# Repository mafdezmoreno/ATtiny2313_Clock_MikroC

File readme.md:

# 7 Segments Display Clock

DIY clock using seven-segment display, ATtiny2313A and optionaly an DHT sensor.

# Structure of this repository

* CAD Files (STL).
* Code for Mikro C Proyect.
* KiCAD proyect with schematic and PCB Design.

## Prerequisites

To carry out this project, it is essential to have a PCB (the one attached in this project or a similar one) in which to solder all the components.

The circuit can also be mounted in an equivalent way on a breadboard following the connection diagram.

A series of electronic components are needed. Below are the recommended components for the realization of the project. Some of them can be replaced by equivalent ones, for example: the value of the resistors, capacitors, mcu (also fucniona with the ATtiny2313), etc.

Compilation and programming tools are also needed. Below are the recommended ones

### Components

List of electronics component nedded:

1. ATtiny2313 (or equivalent)
2. Crystal quartz oscilator 11.0Mhz
3. 4 Digit seven segment display
4. 22pF capacitors
5. Resistor (view schematic)
6. Button switches
7. Some pin 2.54mm connectors 

### Tools needed

1. Programmer. I've used a (Pololu USB AVR Programmer v2)[https://www.pololu.com/product/3170], but you can use another one compatible with the mcu (PICkit, AVRISP XPII... )
2. Compiler. Mikro C AVR Compiler. There are a free versión limited by de memory size of the program to burn into de mcu.
3. Software to load hex file into mcu, using a programmer. I've used (AVRDudess)[https://blog.zakkemble.net/avrdudess-a-gui-for-avrdude/]

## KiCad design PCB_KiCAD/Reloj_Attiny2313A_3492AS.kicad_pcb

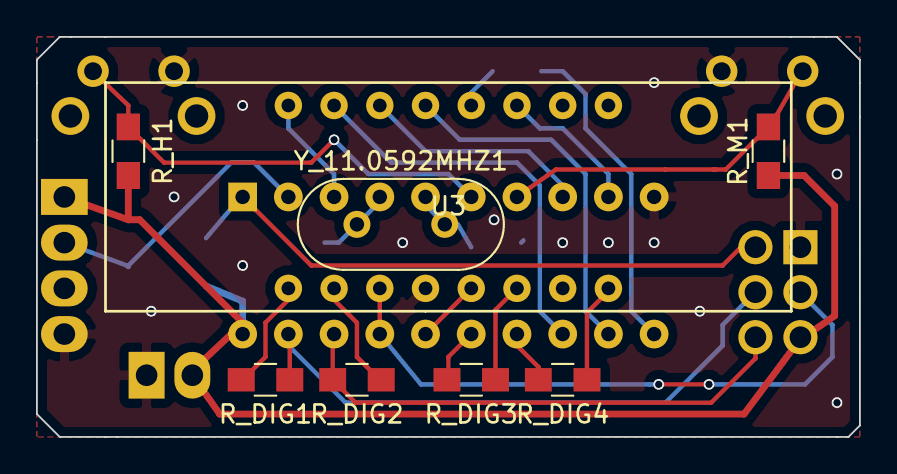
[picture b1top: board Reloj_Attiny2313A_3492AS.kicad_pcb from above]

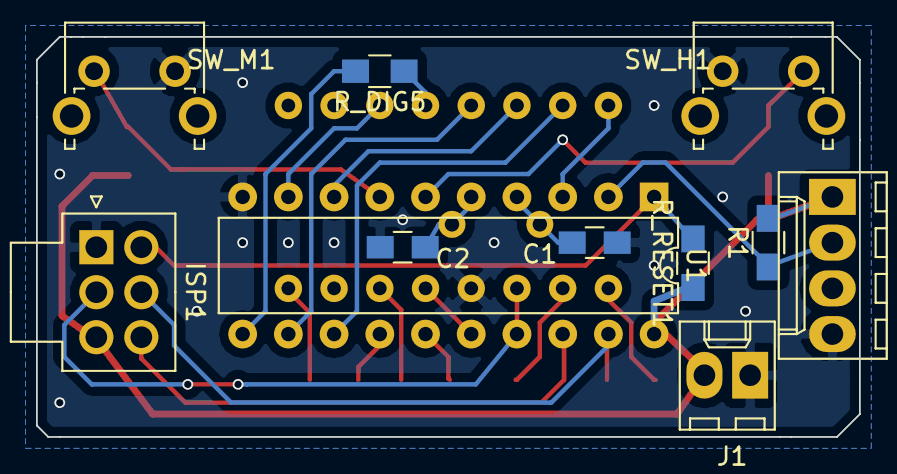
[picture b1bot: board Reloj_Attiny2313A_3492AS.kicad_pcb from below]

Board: 2 copper layers, 45.7 x 22.2 mm, 19 parts (11 on the bottom side), 25 nets.

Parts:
C1, C2: 22pF; C_0805_HandSoldering
DHT_1: DHT11; Molex_KK-6410-04_04x2.54mm_Straight
ISP1: ISP_Conector; Molex_NanoFit_2x03x2.50mm_Straight
J1: Conn_01x02_Male; Molex_KK-6410-02_02x2.54mm_Straight
R1: 10K; R_0805_HandSoldering
R_DIG1, R_DIG2, R_DIG3, R_DIG4, R_DIG5: 560R; R_0805_HandSoldering
R_H1: 10K; R_0805_HandSoldering
R_M1: 10K; R_0805_HandSoldering
R_RESET1: 10K; R_0805_HandSoldering
SW_H1: SW_HORA; SW_Tactile_SPST_Angled_PTS645Vx83-2LFS
SW_M1: SW_MINUTO; SW_Tactile_SPST_Angled_PTS645Vx83-2LFS
U1: ATTINY2313A-PU; DIP-20_W7.62mm
U3: DISPLAY_3492AS_16pin; Display_40mmx13mm_16Pin
Y_11.0592MHZ1: Crystal; Crystal_HC49-4H_Vertical

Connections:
+5V: DHT_1.1, ISP1.3, J1.2, R1.2, R_H1.1, R_M1.1, R_RESET1.1, U1.20
A: U1.8, U3.14
B: U1.3, U3.16
C: U1.12, U3.13
D: ISP1.2, U1.17, U3.3
DIG1: ISP1.5, R_DIG1.1, U1.19
DIG2: ISP1.6, R_DIG2.1, U1.18
DIG3: R_DIG3.1, U1.15
DIG4: R_DIG4.1, U1.14
DPX: R_DIG5.2, U1.11
E: U1.16, U3.5
F: U1.9, U3.11
G: U1.13, U3.15
GND: C1.1, C2.1, DHT_1.4, ISP1.1, J1.1, SW_H1.1, SW_M1.2, U1.10, U3.4
unnamed: C1.2, U1.4, Y_11.0592MHZ1.1
unnamed: C2.2, U1.5, Y_11.0592MHZ1.2
unnamed: DHT_1.2, R1.1, U1.2
unnamed: R_DIG1.2, U3.1
unnamed: R_DIG2.2, U3.2
unnamed: R_DIG3.2, U3.6
unnamed: R_DIG4.2, U3.8
unnamed: R_DIG5.1, U3.12
unnamed: R_H1.2, SW_H1.2, U1.6
unnamed: R_M1.2, SW_M1.1, U1.7
RST: ISP1.4, R_RESET1.2, U1.1

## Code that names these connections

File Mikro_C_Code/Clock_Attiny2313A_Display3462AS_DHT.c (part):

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PUNTOS    PD6 NO NECESITA ACTIVAR GND PARA DRENAGE. DIRECTAMENTE CONECTADO A GND)

PINES DE DRENAJE:
DIG1     PB7
DIG2     PB6
DIG3     PB4
DIG4     PB2

INTERRUPTORES DE CAMBIO DE HORA
MINUTO        PD3 (INT1)
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    PUNTO = 0;

    // Pines drenaje corriente:
    DIG1 = 1;
    DIG2 = 1;
    DIG3 = 1;
    DIG4 = 1;
    Delay_us(500);
}

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    //PUNTO = 0;

    // Pines drenaje corriente:
    DIG1 = 1;
    DIG2 = 1;
    DIG3 = 1;
    DIG4 = 1;
//
}

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
  switch (posicion){
  case 1:
       DIG1=0;  //Establezco la salida en LOW para que drene corriente
       DIG2=1;
       DIG3=1;
       DIG4=1;
       break;
  case 2:
       DIG2=0;
       DIG1=1;
       DIG3=1;
       DIG4=1;
       break;
  case 3:
       DIG3=0;
       DIG2=1;
       DIG1=1;
       DIG4=1;
       break;
  case 4:
       DIG4=0;
       DIG2=1;
       DIG3=1;
       DIG1=1;
       break;
  //
  }
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
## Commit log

2020-12-14 Initial Commit. DIY Clock. Code. PCB layout. 3D STL
    Clock based on the ATtiny2313A, using a sevent segment display and a DHT (humidity temperature) sensor. High precision thanks to quartz crystal.
    Code created to be comiled using MikroC
2020-12-16 doc: Readme.md
    Indication of the necessary tools
    Indication of the necessary basic electronic components
    Repository structure and included files.
2023-08-18 Typos readme.md
